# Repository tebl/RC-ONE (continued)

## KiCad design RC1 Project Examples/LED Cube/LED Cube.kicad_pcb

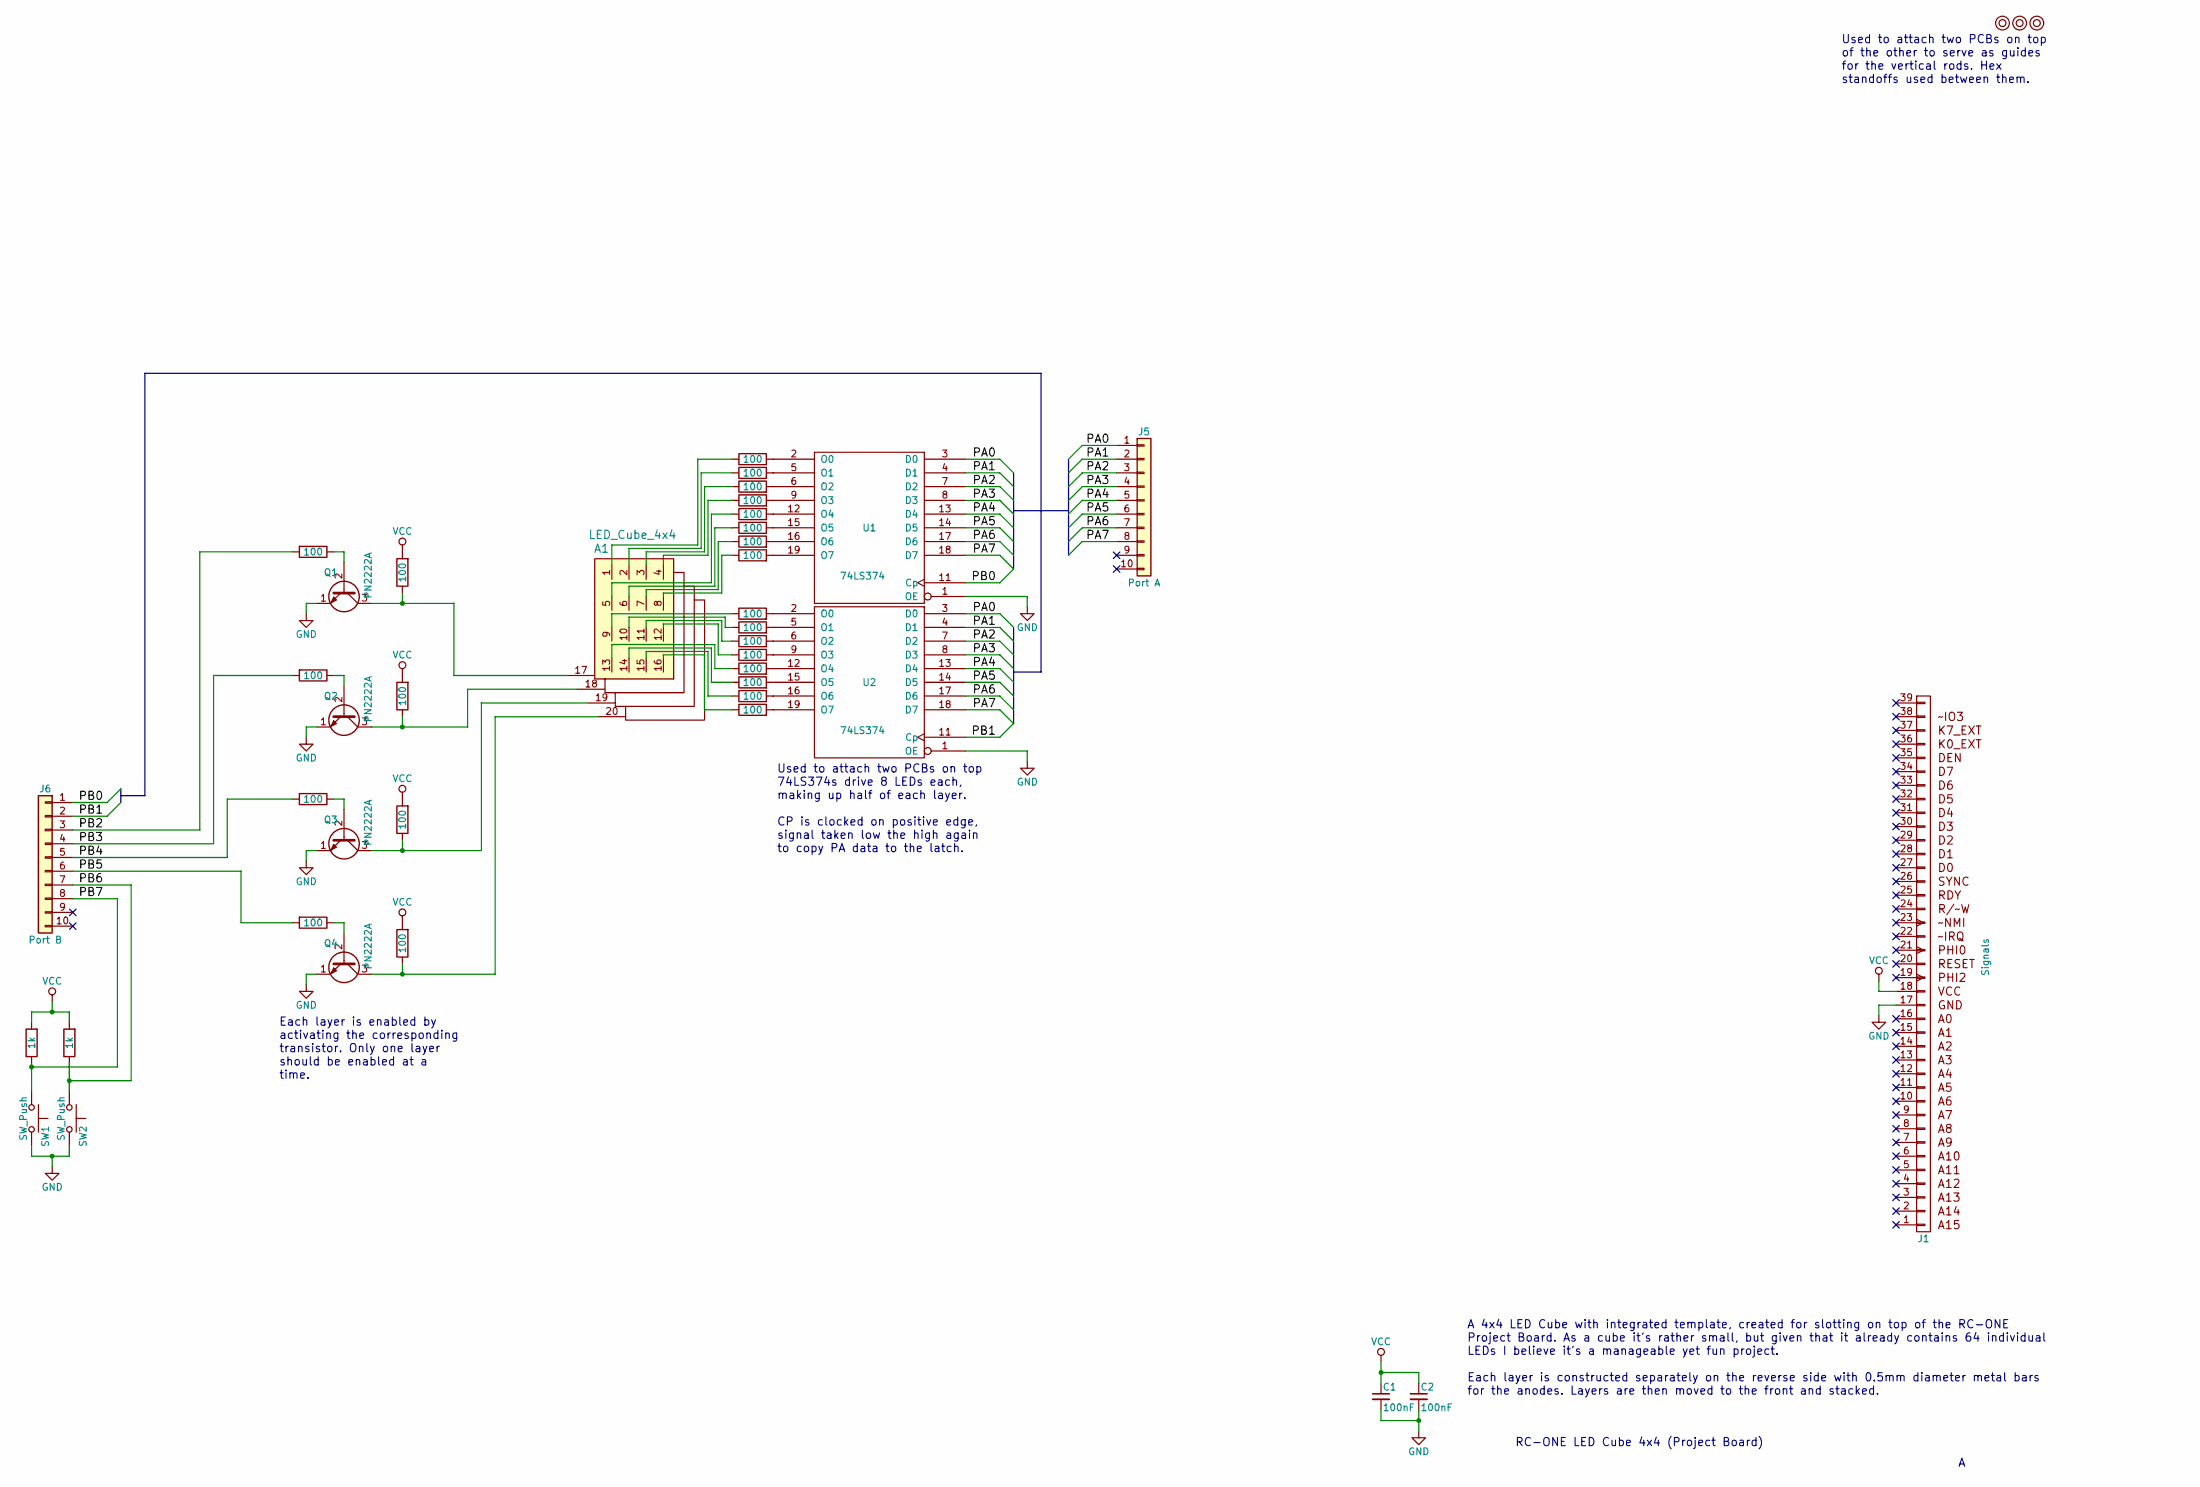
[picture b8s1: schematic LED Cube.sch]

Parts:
A1: LED_Cube_4x4
C1, C2: 100nF; C_Disc_D4.7mm_W2.5mm_P5.00mm
J1: Signals; Pin_Header_Straight_1x39_Pitch2.54mm
J5: Port A; Pin_Header_Straight_1x10_Pitch2.54mm
J6: Port B; Pin_Header_Straight_1x10_Pitch2.54mm
M1, M2, M3: Mounting; 1pin
Q1, Q2, Q3, Q4: PN2222A; TO-92_Molded_Narrow
R1, R2, R3, R4, R5, R6, R7, R8, R9, R10, R11, R12, R15, R16, R17, R18, R19, R20, R21, R22, R23, R24, R25, R26: 100; R_Axial_DIN0207_L6.3mm_D2.5mm_P10.16mm_Horizontal
R13, R14: 1k; R_Axial_DIN0207_L6.3mm_D2.5mm_P10.16mm_Horizontal
SW1, SW2: SW_Push; SW_PUSH_6mm
U1, U2: 74LS374; DIP-20_W7.62mm_Socket_LongPads

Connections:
/PA0: J5.1, U1.3 (D0), U2.3 (D0)
/PA1: J5.2, U1.4 (D1), U2.4 (D1)
/PA2: J5.3, U1.7 (D2), U2.7 (D2)
/PA3: J5.4, U1.8 (D3), U2.8 (D3)
/PA4: J5.5, U1.13 (D4), U2.13 (D4)
/PA5: J5.6, U1.14 (D5), U2.14 (D5)
/PA6: J5.7, U1.17 (D6), U2.17 (D6)
/PA7: J5.8, U1.18 (D7), U2.18 (D7)
/PB0: J6.1, U1.11 (Cp)
/PB1: J6.2, U2.11 (Cp)
/PB2: J6.3, R1.2
/PB3: J6.4, R2.2
/PB4: J6.5, R3.2
/PB5: J6.6, R4.2
/PB6: J6.7, R14.1, SW2.1
/PB7: J6.8, R13.1, SW1.1
GND: C1.2, C2.2, J1.17, Q1.1 (E), Q2.1 (E), Q3.1 (E), Q4.1 (E), SW1.2, SW2.2, U1.1 (OE), U1.10 (GND), U2.1 (OE), U2.10 (GND)
unnamed: A1.1 (la1), R8.1
unnamed: A1.2 (la2), R10.1
unnamed: A1.3 (la3), R11.1
unnamed: A1.4 (la4), R12.1
unnamed: A1.5 (la5), R15.1
unnamed: A1.6 (la6), R16.1
unnamed: A1.7 (la7), R17.1
unnamed: A1.8 (la8), R18.1
unnamed: A1.9 (la9), R19.1
unnamed: A1.10 (la10), R20.1
unnamed: A1.11 (la11), R21.1
unnamed: A1.12 (la12), R22.1
unnamed: A1.13 (la13), R23.1
unnamed: A1.14 (la14), R24.1
unnamed: A1.15 (la15), R25.1
unnamed: A1.16 (la16), R26.1
unnamed: A1.17 (layer0), Q1.3 (C), R9.1
unnamed: A1.18 (layer1), Q2.3 (C), R5.1
unnamed: A1.19 (layer2), Q3.3 (C), R6.1
unnamed: A1.20 (layer3), Q4.3 (C), R7.1
unnamed: Q1.2 (B), R1.1
unnamed: Q2.2 (B), R2.1
unnamed: Q3.2 (B), R3.1
unnamed: Q4.2 (B), R4.1
unnamed: R8.2, U1.2 (O0)
unnamed: R10.2, U1.5 (O1)
unnamed: R11.2, U1.6 (O2)
unnamed: R12.2, U1.9 (O3)
unnamed: R15.2, U1.12 (O4)
unnamed: R16.2, U1.15 (O5)
unnamed: R17.2, U1.16 (O6)
unnamed: R18.2, U1.19 (O7)
unnamed: R19.2, U2.2 (O0)
unnamed: R20.2, U2.5 (O1)
unnamed: R21.2, U2.6 (O2)
unnamed: R22.2, U2.9 (O3)
unnamed: R23.2, U2.12 (O4)
unnamed: R24.2, U2.15 (O5)
unnamed: R25.2, U2.16 (O6)
unnamed: R26.2, U2.19 (O7)
VCC: C1.1, C2.1, J1.18, R5.2, R6.2, R7.2, R9.2, R13.2, R14.2, U1.20 (VCC), U2.20 (VCC)

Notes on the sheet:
RC-ONE LED Cube 4x4 (Project Board)
A 4x4 LED Cube with integrated template, created for slotting on top of the RC-ONE Project Board. As a cube it's rather small, but given that it already contains 64 individual LEDs I believe it's a manageable yet fun project. Each layer is constructed separately on the reverse side with 0.5mm diame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
Used to attach two PCBs on top of the other to serve as guides for the vertical rods. Hex standoffs used between them.
Used to attach two PCBs on top 74LS374s drive 8 LEDs each, making up half of each layer. CP is clocked on positive edge, signal taken low the high again to copy PA data to the latch.
Each layer is enabled by activating the corresponding transistor. Only one layer should be enabled at a time.

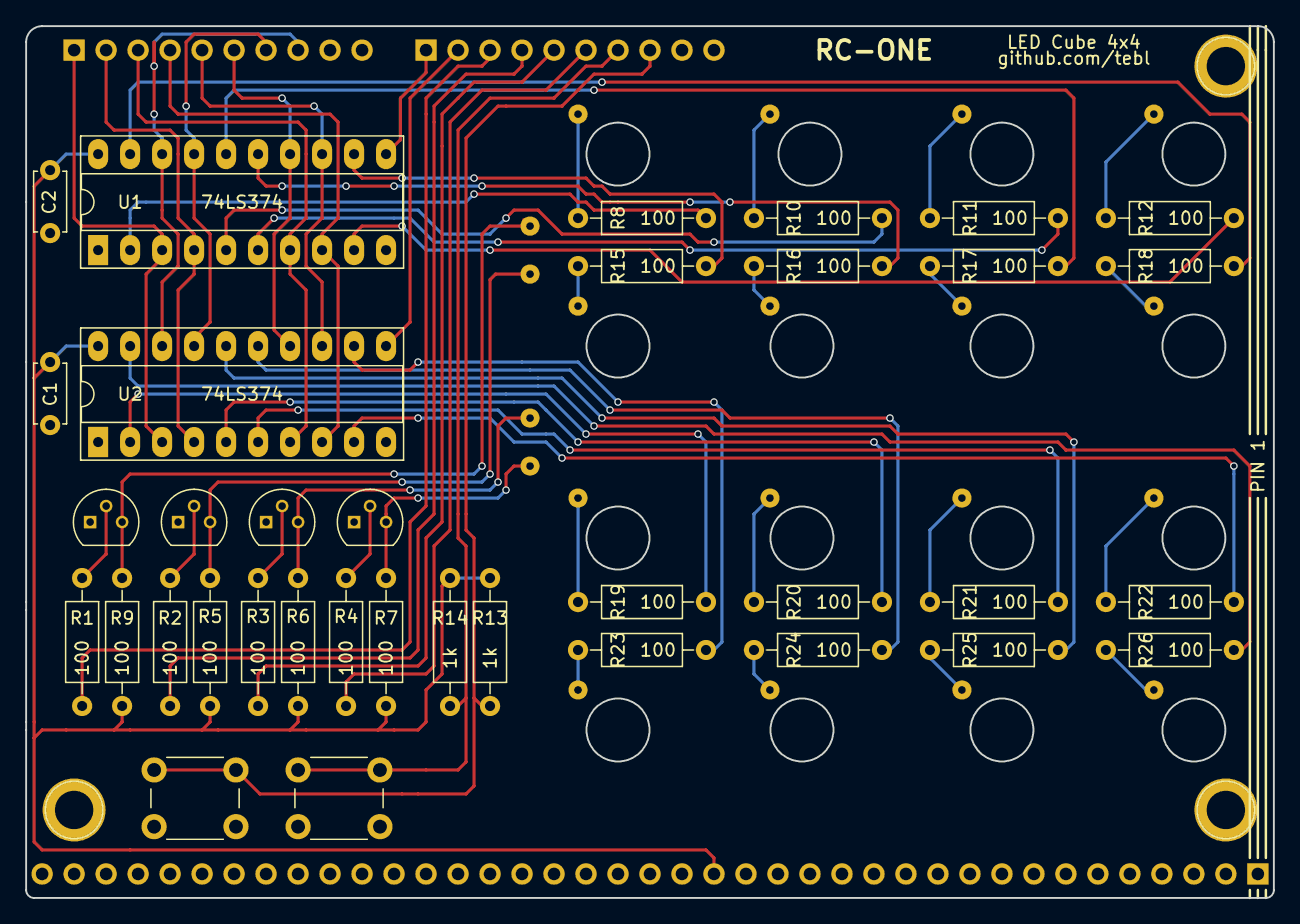
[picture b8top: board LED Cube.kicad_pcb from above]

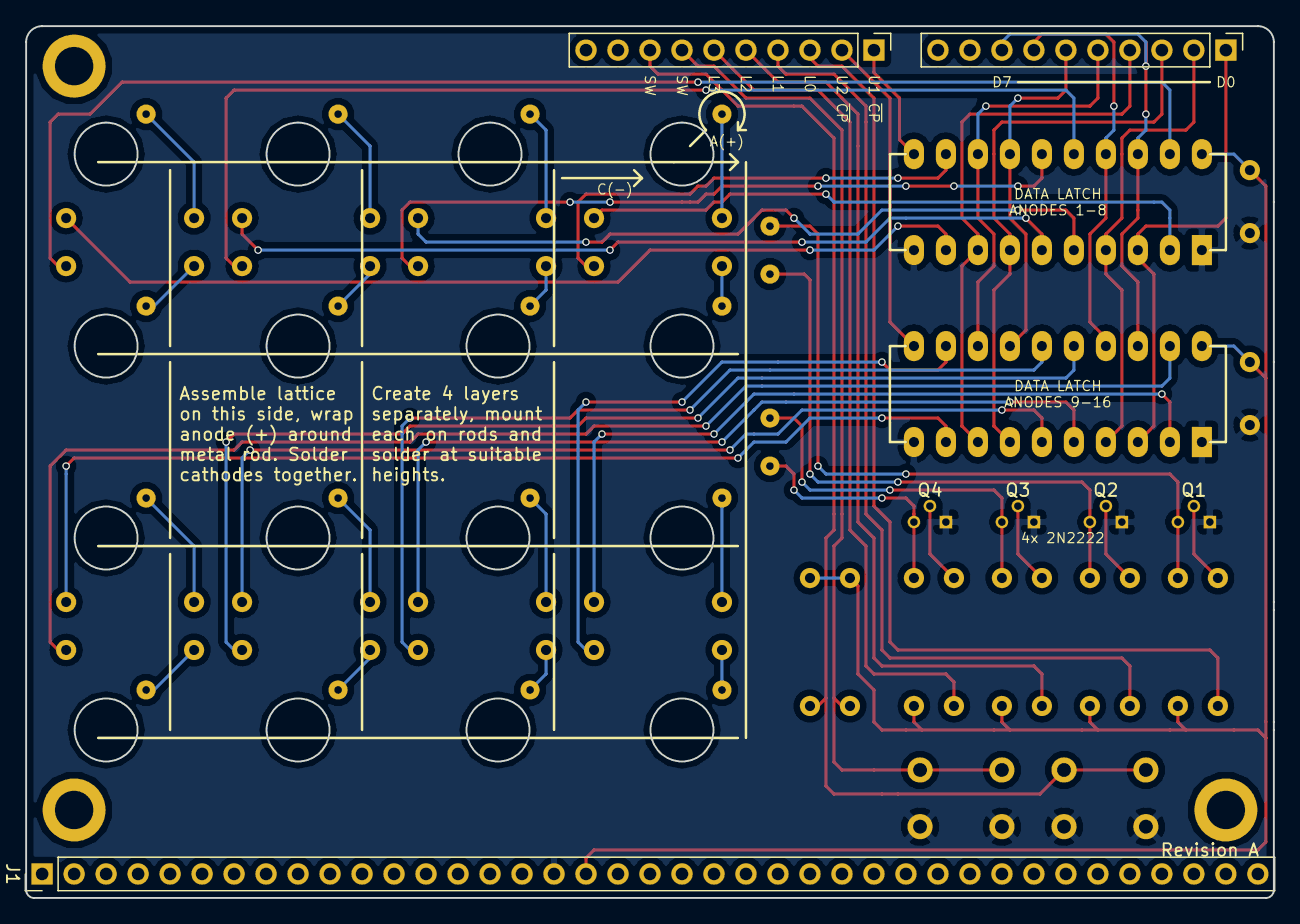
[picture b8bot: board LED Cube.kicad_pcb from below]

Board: 2 copper layers, 99.1 x 69.2 mm, 43 parts (3 on the bottom side), 58 nets.

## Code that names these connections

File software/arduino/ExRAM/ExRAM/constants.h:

#define VERSION "0.3"
#define BAUD_RATE 115200
#define MAX_INPUT_SIZE 100
#define MAX_MEMORY_SIZE 8192
#define TERMINAL_COLS 80
//#define DEBUG

/* Pin definitions */
#define SHIFT_DATA 2
#define SHIFT_CLK 3
#define SHIFT_LATCH 4

#define EX_D0 6
#define EX_D7 13
#define EX_A13 14
#define EX_A14 15
#define EX_RnW 16
#define EX_CS 19

#define EX_CONTROL 5
#define EX_RESET 17

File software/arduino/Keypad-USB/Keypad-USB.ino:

#include "Keyboard.h"

#define ROW0 0
#define ROW0_0 0
#define ROW0_1 1
#define ROW0_2 2
#define ROW0_3 3
#define ROW0_4 4
#define ROW0_5 5
#define ROW0_6 6
#define ROW1 1
#define ROW1_7 0 
#define ROW1_8 1
#define ROW1_9 2 
#define ROW1_A 3 
#define ROW1_B 4 
#define ROW1_C 5 
#define ROW1_D 6 
#define ROW2 2
#define ROW2_E 0 
#define ROW2_F 1 
#define ROW2_AD 2 
#define ROW2_DA 3 
#define ROW2_PLUS 4 
#define ROW2_GO 5 
#define ROW2_PC 6
#define ROW3 3 /* virtual row for debouncing */
#define ROW3_RS 0
#define ROW3_ST 1
#define ROW3_SST 2

#define ST_PIN 14
#define RS_PIN 15
#define SST_PIN 18
#define LED_PIN 19
#define NUM_COLS 7
#define NUM_ROWS 3
byte colPins[NUM_COLS] = {2, 3, 4, 5, 6, 7, 8};
byte rowPins[NUM_ROWS] = {9, 10, 16};

#define DEBOUNCE_VALUE 250
#define REPEAT_DELAY 1200
int debounceCount[NUM_ROWS + 1][NUM_COLS];

bool SST_EN = false;

void setup() {
  Serial.begin(115200);

  pinMode(ST_PIN, INPUT_PULLUP);
  pinMode(RS_PIN, INPUT_PULLUP);
  pinMode(SST_PIN, INPUT_PULLUP);
  pinMode(LED_PIN, OUTPUT);

  // set all pins as inputs and activate pullups
  for (byte c = 0; c < NUM_COLS; c++) {
    pinMode(colPins[c], INPUT);
    digitalWrite(colPins[c], HIGH);

    // clear debounce counts
    for (byte r = 0; r < NUM_ROWS; r++) {
      debounceCount[r][c] = 0;
    }
  }

  // set all pins as inputs
  for (byte r = 0; r < NUM_ROWS; r++) {
    pinMode(rowPins[r], INPUT);
  }

  Keyboard.begin();
}

void loop() {
  if (check_debounced(RS_PIN, 3, ROW3_RS, false)) handle_key(ROW3, ROW3_RS);
  if (check_debounced(ST_PIN, 3, ROW3_ST, false)) handle_key(ROW3, ROW3_ST);
  check_sst();

  for (byte row = 0; row < NUM_ROWS; row++) {
    // turn the row on
    pinMode(rowPins[row], OUTPUT);
    digitalWrite(rowPins[row], LOW);

    for (byte col = 0; col < NUM_COLS; col++) {
      if (check_debounced(
          colPins[col], 
          row, 
          col, 
          is_repeatable(row, col)
        )) {
        handle_key(row, col);
      }
    }

    // turn the row back off
    pinMode(rowPins[row], INPUT);
  }
}

/*
 * Reads the specified digital pins, debouncing is performed in order
 * to ignore erroneous key-presses due to the mechanical nature of the
 * switches themselves. d_row/d_col is indexes used to keep track of how
 * long a key has been depressed, a key will normally only register as
 * pressed as long as the reading has been stable for a reasonable amount
 * of time. allow_repeat specifies wether a key held down will register as
 * subsequent presses, or if it should be ignored until key has been
 * released.
 */
bool check_debounced(byte pin, byte d_row, byte d_col, bool allow_repeat) {
  if (digitalRead(pin) == LOW) {
    debounceCount[d_row][d_col]++;

    // has the switch been pressed continually for long enough?
    int count = debounceCount[d_row][d_col];
    if (count == DEBOUNCE_VALUE) {
      return true;
    } else if (count > DEBOUNCE_VALUE) {
      if (count == (DEBOUNCE_VALUE + REPEAT_DELAY)) {
        debounceCount[d_row][d_col] = DEBOUNCE_VALUE + 1;

        if (allow_repeat) return true;
        else return false;
      }
    }
  } else {
    // not pressed, reset debounce count
    debounceCount[d_row][d_col] = 0;
  }
  
  return false;
}

/*
 * Evaluates wether a key should be directly repeatable, a key
 * that is not repeatable will not recognize any further presses
 * until it has been released.
 */
bool is_repeatable(byte row, byte col) {
  if (row == ROW2) {
    switch (col) {
      case ROW2_AD:
      case ROW2_DA:
      case ROW2_GO:
      case ROW2_PC:
        return false;
      default:
        return true;
    }
  }
  return true;
}

/*
 * Monitor SST switch for changes, both state transitions are
 * debounced like the rest of the keys. Handled separately as
 * it is a locking key, something not normally found on a
 * keyboard.
 */
void check_sst() {
  if (SST_EN) {
    if (digitalRead(SST_PIN) == HIGH) {
      debounceCount[ROW3][ROW3_SST]++;
      int count = debounceCount[ROW3][ROW3_SST];
      if (count == DEBOUNCE_VALUE) {
        SST_EN = false;
        handle_sst_off();
      }
    }
  } else {
    if (check_debounced(SST_PIN, 3, 2, false)) {
      debounceCount[ROW3][ROW3_SST] = 0;
      SST_EN = true;
      handle_sst_on();
    }
  }
}

void handle_sst_on() {
  handle_key(ROW3, ROW3_SST);
  Serial.println("SST enabled!");
  digitalWrite(LED_PIN, HIGH);
}

void handle_sst_off() {
  handle_key(ROW3, ROW3_SST);
  Serial.println("SST disabled!");
  digitalWrite(LED_PIN, LOW);
}

/*
 * Translate keypad keys to their equivalents found on a modern
 * keyboard.
 */
void handle_key(byte row, byte col) {
  if (row == ROW0) {
    switch(col) {
      case ROW0_0: Keyboard.write('0'); return;
      case ROW0_1: Keyboard.write('1'); return;
      case ROW0_2: Keyboard.write('2'); return;
      case ROW0_3: Keyboard.write('3'); return;
      case ROW0_4: Keyboard.write('4'); return;
      case ROW0_5: Keyboard.write('5'); return;
      case ROW0_6: Keyboard.write('6'); return;
    }
  }

  if (row == ROW1) {
    switch(col) {
      case ROW1_7: Keyboard.write('7'); return;
      case ROW1_8: Keyboard.write('8'); return;
      case ROW1_9: Keyboard.write('9'); return;
      case ROW1_A: Keyboard.write('A'); return;
      case ROW1_B: Keyboard.write('B'); return;
      case ROW1_C: Keyboard.write('C'); return;
      case ROW1_D: Keyboard.write('D'); return;
    }
  }

  if (row == ROW2) {
    switch(col) {
      case ROW2_E: Keyboard.write('E'); return;
      case ROW2_F: Keyboard.write('F'); return;
      case ROW2_AD: Keyboard.write('/'); return;
      case ROW2_DA: Keyboard.write('*'); return;
      case ROW2_PLUS: Keyboard.write('+'); return;
      case ROW2_GO: Keyboard.write('F'); return;
      case ROW2_PC: Keyboard.write('F'); return;
    }
  }

  if (row == ROW3) {
    switch(col) {
      case ROW3_RS: Keyboard.write(0xB1); return;
      case ROW3_ST: Keyboard.write('S'); return;
      case ROW3_SST: Keyboard.write(0x2A); return;
    }
  }
}

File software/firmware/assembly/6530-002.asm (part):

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GET1    BIT     SAD         CHECK IF TTY-MODE
        BNE     GET6         IF NO

; PA7 is input TTY
        BMI     GET1        WAIT FOR STARTBIT
        JSR     DELAY       DELAY 1 BIT
;
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        STX     MODE
;
INIT1   LDX     #$00
        STX     PADD        PA0..PA7 = INPUT
        LDX     #$3F
        STX     PBDD        PB0..PB5 = OUTPUT
;                           PB6, PB7 = INPUT
        LDX     #$07        ENABLE 74145 OUTPUT 3 TO
        STX     SBD          CHECK KB/TTY-MODE
        CLD
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AKA     STX     SBD         OUTPUT DIGIT
        INX                 GET NEXT DIGIT
        INX                 
        AND     SAD         A := A && (PA0..PA7)
        DEY                 ALL ROWS DONE?
        BNE     AKA          DO MORE
;
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
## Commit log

2018-09-01 Empty project
2018-09-05 Single Step Circuit
2019-08-25 Keypad schematic
2019-08-25 Added RS/ST/SST to schematic
2019-08-25 Keypad layout done
2019-08-27 CPU schematic drafted
2019-08-27 Added bypass caps and leftover gates
2019-08-27 Routed most signals on CPU board
2019-09-04 Added UI signals to CPU board
2019-09-04 Added serial to UI schematic
2019-09-04 Added phi1 to UI connector
2019-09-05 UI layout done
2019-09-06 Added silkscreen title
2019-09-06 Keypad MX layout tweaked
2019-09-06 UI gerber export
2019-09-06 Keypad SX layout done
2019-09-06 Tweaked silkscreens and exported gerbers for CPU/UI
2019-09-06 Ignore gerber zip-files
2019-09-07 Added ability to override K0/K7
2019-09-07 Added RAM A13/A14 reconnects for external RAM logic
2019-09-08 Decided to connect remaining RAM address lines for external logic.
2019-09-13 Keypad MX SST moved to match original keypad layout
2019-09-13 Keypad SST moved to match original keypad layout
2019-09-13 65K Expansion schematic done
2019-09-16 65K layout and silkscreen done
2019-09-16 Added 65K expansion notice to CPU schematic
2019-09-17 ExRAM Schematic done
2019-09-17 Routed D0-D7
2019-09-17 8K ExRAM layout and silkscreen done
2019-09-21 Moved transistors the right way around
2019-09-22 Gerber export
2019-09-23 RC1 Sound Interface schematic
2019-09-24 Sound Interface layout done
2019-09-24 Wrong schematic name
2019-09-25 Added Real Time Clock (untested and unverified)
2019-09-29 RTC README
2019-09-29 Eliminated 74LS145 from CPU module
2019-09-29 Documentation
2019-09-29 Firmware added
2019-09-29 Set license
2019-09-30 Reworked schematic to remove 74LS145
2019-09-30 Updated keypad schematic for clarity
2019-10-01 KIM-1 vector setup notice
2019-10-01 Assigned new UI footprints
2019-10-01 Layout updated
2019-10-01 Added datasheet
2019-10-02 Updated 65K schematic
2019-10-02 65K layout updated
2019-10-04 Export hex format
2019-10-04 Fixed checksum calculation
2019-10-06 Read Intel Hex format
2019-10-08 Read Paper Tape format
2019-10-08 A7 not usable as digital pin on Nano (appearantly)
2019-10-08 MX Keypad now matches Commodore Kim-1
2019-10-16 Memory test runs
2019-10-16 Fixed hex import
2019-10-16 Fixed paper tape import
2019-10-20 Keypad USB adapter schematic
2019-10-20 Can scan keypad
2019-10-20 Debounced SST switch
2019-10-21 Assigned last keypad keys
2019-10-22 Assigned keypad adapter footprints
2019-10-24 Updated J4 markings on 65K board
2019-10-24 Updated documentation
2019-10-24 Added memory map to README
2019-10-24 Use entire memory map in documentation
2019-10-24 Gallery images (revision A)
2019-10-24 Module notices added
2019-11-03 Added diodes to solve display glitch
2019-11-03 Module list is now table
2019-11-03 Added diodes to UI board
2019-11-03 Keypad to USB layout done
2019-11-07 Gerber export keypad to USB module
2019-11-08 Changed UI resistors to horizontal
2019-11-17 Added pictures
2019-11-17 Added CPU README
2019-11-17 UI README added
2019-11-17 Aded Keypad MX README
2019-11-18 Memory Map as PNG
2019-11-18 65K pictures
2019-11-18 Added 65K Expansion README
2019-11-18 Moved Troubleshooting document
2019-11-19 Manual. Chapter 1.
2019-11-20 KIM-1 add for manual
2019-11-20 KIM-1 picture
2019-11-20 Module pictures
2019-11-20 Changed keypad picture
2019-11-20 Added pinout documentation image
2019-11-20 Added pin alignment picture
2019-11-20 Added documentation image
2019-11-20 Use different image
2019-11-20 Cropped
2019-11-20 Chapter 4
2019-11-21 Moved image
2019-11-21 Chapter 5
2019-11-21 65K Image
2019-11-21 Chapter 6
2019-11-21 Chapter 5.2 and 7
2019-11-21 Added board settings
2019-12-04 Added projects board
2019-12-20 Project board has clock select pins
2019-12-22 LED Cube schematic
2019-12-22 LED Cube schematic updated
2019-12-23 Layout done
2019-12-23 LED Cube 4x4 finishing touches
2019-12-23 Prototyping project board
2019-12-28 Tweak ExRAM signalling
2019-12-31 Project boards moved to separate repository
2020-01-11 Clock example from Kilobaud magazine, february 1977
2020-01-11 Changes to 24 hours
2020-01-11 Tweaks to save Arduino RAM
2020-01-12 Process serial byte-by-byte
2020-01-12 Use ANSI terminal codes (for fun)
2020-01-12 Handle backspace
2020-01-12 Better routines for handling backspace
2020-01-12 Dump marks empty cells
2020-01-12 Added paper-tape export
2020-01-12 Added screenshots
2020-01-12 Handle intel hex end-of-file record by ignoring it
2020-01-13 Updated examples
2020-01-13 Changed status message
2020-01-13 Lock command
2020-01-13 Movit from First book of KIM
2020-01-13 ExRAM gallery image
2020-01-14 Movit changed for ExRAM
2020-01-14 Speedup by removing delays
2020-01-14 Movit now runs properly
2020-01-14 Movit moved to 3F70
2020-01-14 Moved clock to 0200
2020-01-17 6530-002 assembly source
2020-01-17 Added N.C. to pin 39
2020-01-17 6530-003 assembly source
2020-01-17 Deorganized firmware files
2020-01-17 Movit pages in PDF-format
2020-01-17 Movit README
2020-01-17 Updated PDF-links
2020-01-18 Prepare for other parts of firmware
2020-01-18 Added short README on monitor code sources
2020-01-21 65K Expansion silkscreen updated
2020-01-21 ExRAM silkscreen updated
2020-01-22 RTC untested notice
2020-01-23 Address calculations fixed
2020-01-23 Fixed RTC address calculations
2020-01-25 Mark pin 1
2020-01-25 Compact Flash
2020-01-25 Added buffer to Compact Flash
2020-01-25 Gerber uodate
2020-01-27 Updated pad dimensions for Arduino Pro Micro
2020-01-27 Small board to relocate UI keypad connector
2020-01-29 TMS9918 schematic
2020-01-29 TMS9918 layout
2020-02-09 Added game board to memory map
2020-03-02 ACIA Microchess (untested)
2020-10-16 Updated some README files
2020-10-16 Attempted ExRAM memory backup
2020-10-17 ExRAM gerber export new version
2020-10-17 Updated ACIA to make it work with external oscillator
2020-10-18 ACIA program example
2020-10-18 Add board picture
2020-10-18 Removed non-working example
2020-10-18 CPU/UI updated to KiCad 5
2020-11-27 Converted ExRAM firmware to PlatformIO
2020-11-27 Fixed warnings
2020-11-27 Moved dump commands into separate files
2020-11-27 Moved memory and exram functions
2020-11-27 Fix buffer overflow
2020-11-27 Added peek/poke commands
2020-11-29 Separate SRAM CS control
2020-11-29 Updated memory map
2020-12-01 Updated schematic to match prototype
